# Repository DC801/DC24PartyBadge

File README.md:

# DC801_DC24PartyBadge
Party badge and BLE hardware board

# Hardware
Board design is in Eagle

Board consists of:

Rigado BMD-200 Bluetooth low energy based on a Nordic nRF51822
 - 16MHz ARM® Cortex™ M0 CPU, 256kB of flash memory, 32kB RAM
 - https://www.rigado.com/product/bmd-200/

 - 2 RGB LEDs
 - 10 orange LEDs addressable in pairs
 - Single button
 - A MCP73831 LiPo battery charger
 - Spare pins (I2C)
 - JTAG interface
 - Micro USB - for charging only
 - Kickass silkscreen

# Software
Environment is the nRFgo Studio and Keil
need a segger j-link programmer
custom_board.h goes in the C:\Keil_v5\ARM\Pack\NordicSemiconductor\nRF_Examples\11.0.0-2.alpha\bsp
Uses the soft device s130v1 firmware

Device is programmed with the softdevice first, then the application is loaded

# What's it do?

The badge, when powered on, will run in one of 5 modes.

- Mode 1 - 'Knight Rider' pattern
- Mode 2 - Alternating red eyes
- Mode 3 - Color strobe eyes
- Mode 4 - Battery indicator - voltage as a percentage of 3.7V.  Each pair lit is 20%, flashing means 10% instead - add the pairs together to get percentage (increases to the right)
- Mode 5 - Randomly firing orange LEDs

In all modes the bluetooth stack is working as an Eddystone, which broadcasts a URL every 100ms.  Newer phones will automatically see the URL and display a notification for it.

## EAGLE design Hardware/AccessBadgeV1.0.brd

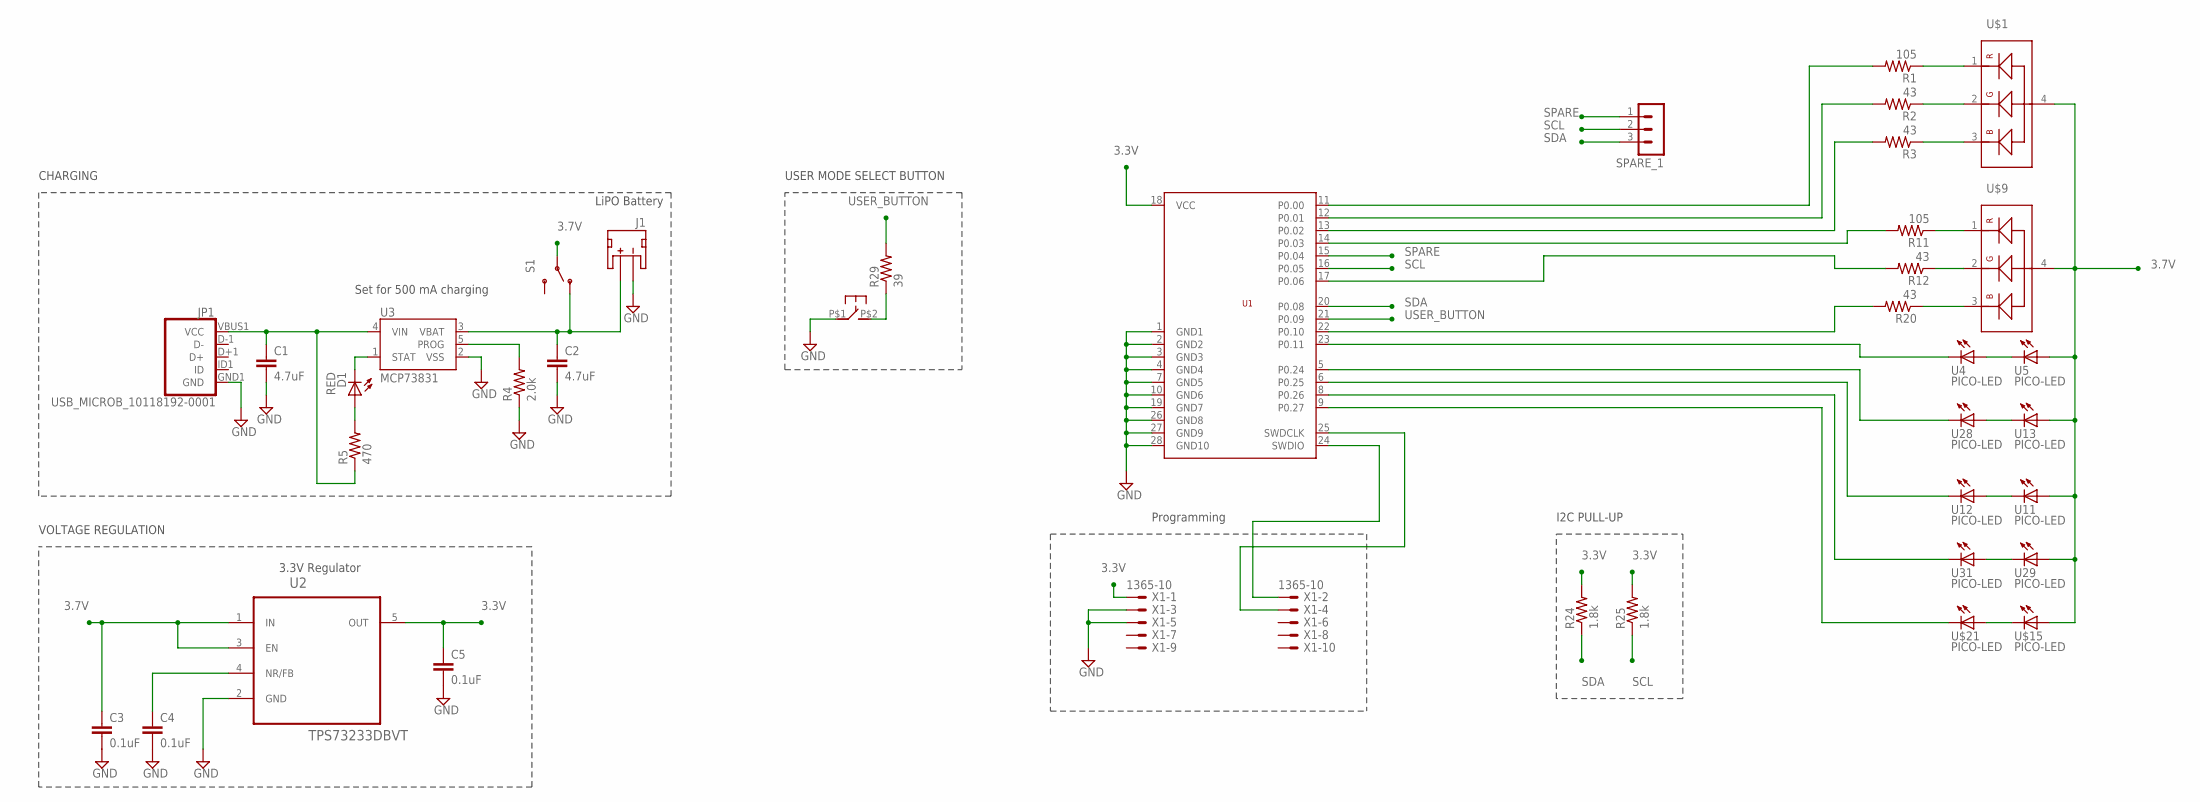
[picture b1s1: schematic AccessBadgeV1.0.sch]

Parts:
C1, C2: 4.7uF; 0603-CAP
C3, C4, C5: 0.1uF; C0201
D1: RED; CHIP-LED0603
J1: JST_2MM_MALE; JST-2-SMD
JP1: USB_MICROB_10118192-0001; USB-B-MICRO-SMD_V03
R1, R11: 105; R0201
R2, R3, R12, R20: 43; R0201
R4: 2.0k; R0201
R5: 470; R0201
R24, R25: 1.8k; R0201
R29: 39; R0201
S1: SWITCH-SPDTSMD2; SWITCH-SPDT-SMD
SLC: TACTILE_BUTTON; KXT131
SPARE_1: MA03-1
U1: BMD-200
U2: TPS73233DBVT; SOT95P280X145-5N
U3: MCP73831; SOT23-5
U4, U5, U11, U12, U13, U28, U29, U31: PICO-LED; CHIP-LED0402
U$1, U$9: RGB; 0606
U$15, U$21: PICO-LED; CHIP-LED0402
X1: 1365-10

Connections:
3.3V: C5.1, R24.2, R25.2, U1.18 (VCC), U2.5 (OUT), X1.1
3.7V: C3.1, S1.2, U2.1 (IN), U2.3 (EN), U5.P$1 (A), U11.P$1 (A), U13.P$1 (A), U29.P$1 (A), U$1.4, U$9.4, U$15.P$1 (A)
GND: C1.2, C2.2, C3.2, C4.2, C5.2, J1.1 (-), JP1.GND1 (GND), R4.1, SLC.P$1, U1.1 (GND1), U1.2 (GND2), U1.3 (GND3), U1.4 (GND4), U1.7 (GND5), U1.10 (GND6), U1.19 (GND7), U1.26 (GND8), U1.27 (GND9), U1.28 (GND10), U2.2 (GND), U3.2 (VSS), X1.3, X1.5
unnamed: R1.2, U1.11 (P0.00)
unnamed: R2.2, U1.12 (P0.01)
unnamed: R3.2, U1.13 (P0.02)
unnamed: R11.2, U1.14 (P0.03)
unnamed: U1.5 (P0.24), U28.P$2 (C)
unnamed: U1.9 (P0.27), U$21.P$2 (C)
unnamed: U4.P$1 (A), U5.P$2 (C)
unnamed: U1.23 (P0.11), U4.P$2 (C)
unnamed: R1.1, U$1.1
unnamed: R2.1, U$1.2
unnamed: R3.1, U$1.3
unnamed: R4.2, U3.5 (PROG)
unnamed: C1.1, JP1.VBUS1 (VCC), R5.1, U3.4 (VIN)
unnamed: D1.A, R5.2
unnamed: D1.C, U3.1 (STAT)
unnamed: R11.1, U$9.1
unnamed: R12.1, U$9.2
unnamed: C4.1, U2.4 (NR/FB)
unnamed: U$15.P$2 (C), U$21.P$1 (A)
unnamed: U29.P$2 (C), U31.P$1 (A)
unnamed: U11.P$2 (C), U12.P$1 (A)
unnamed: U13.P$2 (C), U28.P$1 (A)
unnamed: R20.1, U$9.3
unnamed: U1.8 (P0.26), U31.P$2 (C)
unnamed: U1.6 (P0.25), U12.P$2 (C)
unnamed: R20.2, U1.22 (P0.10)
unnamed: R12.2, U1.17 (P0.06)
unnamed: R29.1, SLC.P$2
unnamed: U1.24 (SWDIO), X1.2
unnamed: U1.25 (SWDCLK), X1.4
SCL: R25.1, SPARE_1.2, U1.16 (P0.05)
SDA: R24.1, SPARE_1.3, U1.20 (P0.08)
SPARE: SPARE_1.1, U1.15 (P0.04)
USER_BUTTON: R29.2, U1.21 (P0.09)
VBAT1: C2.1, J1.2 (+), S1.1 (O), U3.3 (VBAT)

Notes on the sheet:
Programming
I2C PULL-UP
LiPO Battery
Set for 500 mA charging
3.3V Regulator
USER MODE SELECT BUTTON
CHARGING
VOLTAGE REGULATION

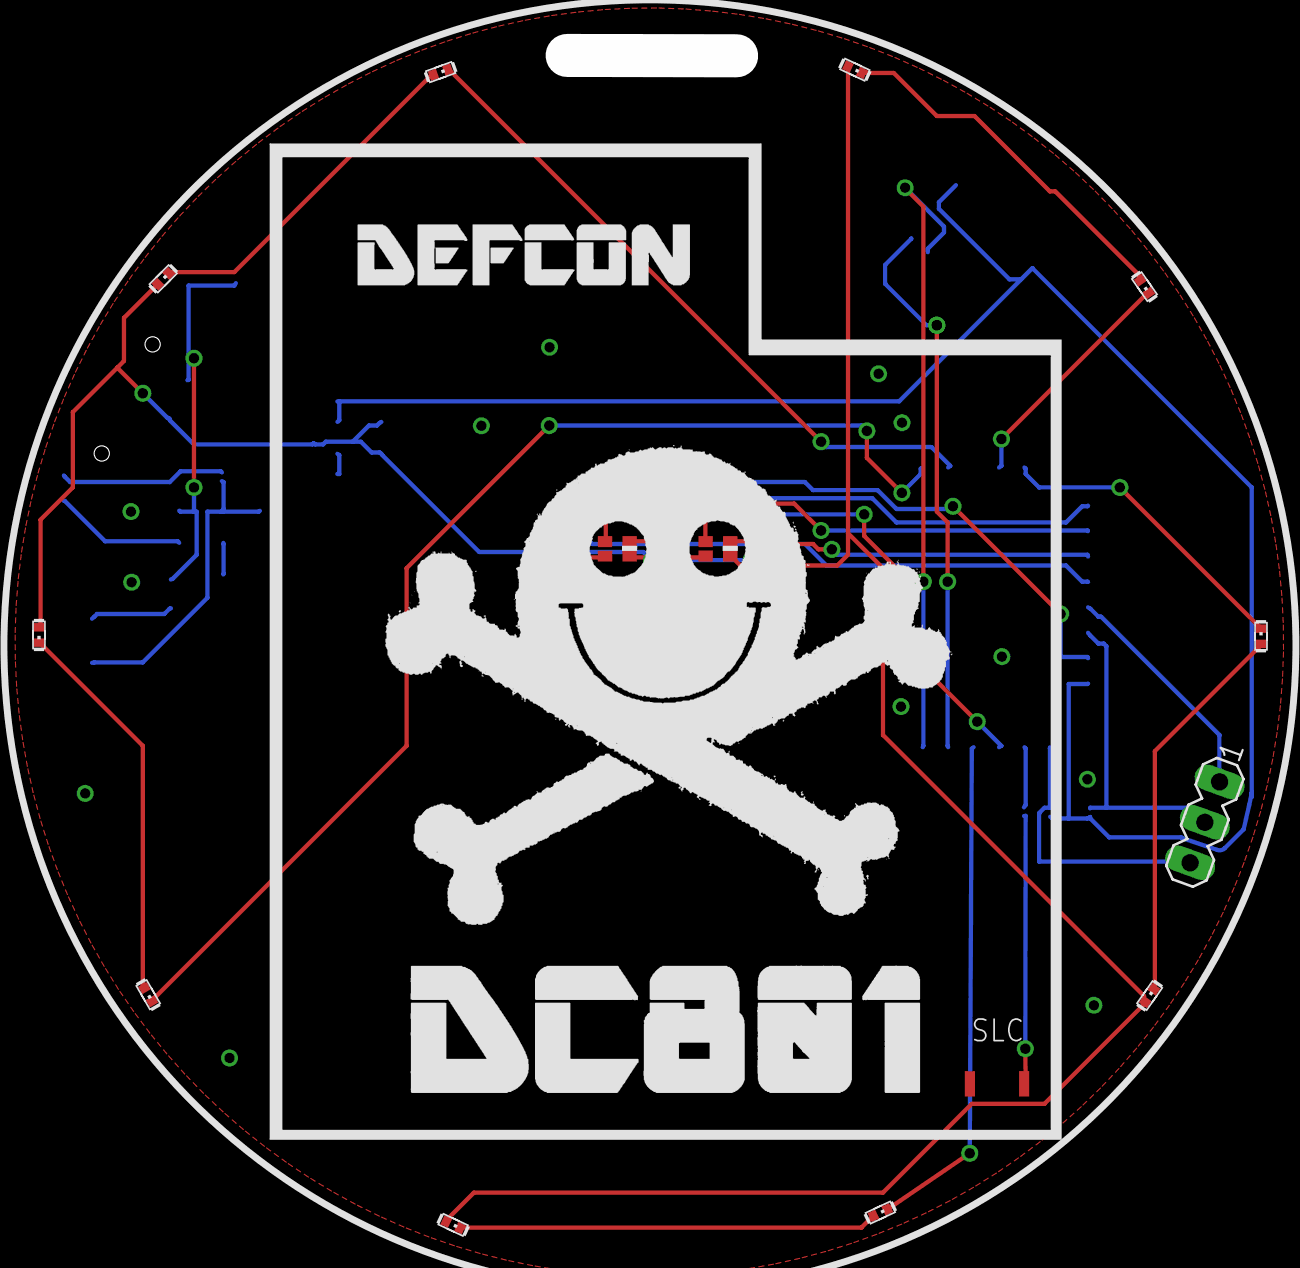
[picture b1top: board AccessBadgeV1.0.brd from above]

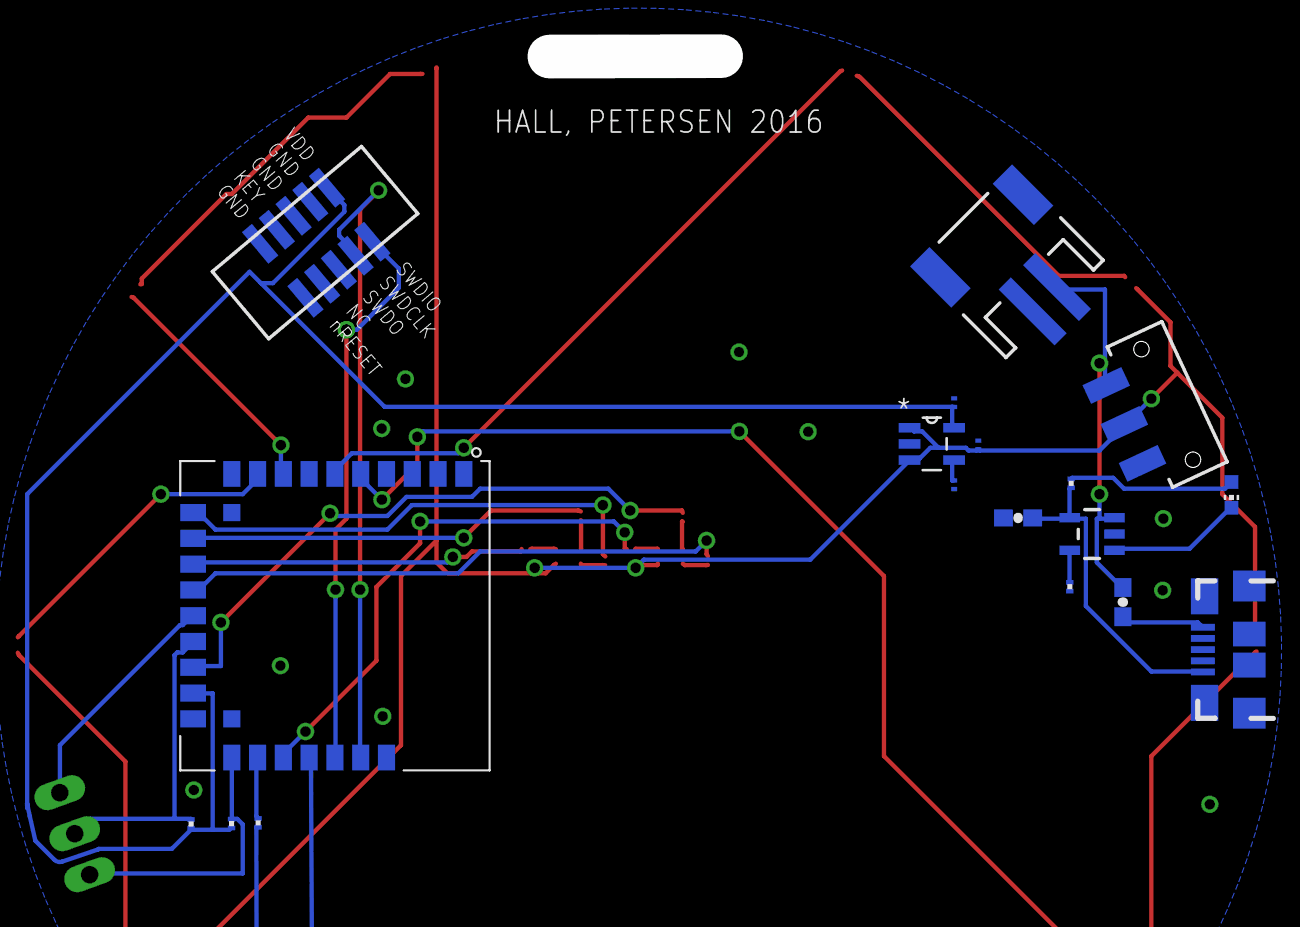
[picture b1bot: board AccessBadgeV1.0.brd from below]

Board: 2 copper layers, 38 parts (18 on the bottom side), 38 nets.

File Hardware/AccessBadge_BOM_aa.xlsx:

Mfg Part # | Ref. Des. | Description Value Pkg |  |  |  | QTY | DNI | NOTES
CL10A475KQ5LNNC | C1, C2 | CAPACITOR, 4.7uF, C0603 |  |  |  | 2
GRM033R60J104KE19D | C3, C4, C5 | CAPACITOR, 0.1uF, C0201 |  |  |  | 3
SML-D12V1WT86 | D1 | RED, LEDCHIP-LED0603 |  |  |  | 1
S2B-PH-SM4-TB(LF)(SN) | J1 | JST_2MM_MALE, JST-2-SMD, Mates to single-cell LiPo batteries |  |  |  | 1
10118192-0001LF | JP1 | USB_MICROB_PLUGCONN-11752, USB-B-MICRO-SMD_V03, USB Micro-B Plug |  |  |  | 1
3220-10-0300-00 | x1 | 10 Positions Header, Shrouded Connector 0.050" (1.27mm) Surface Mount Gold |  |  |  | 1 |  | Digikey # 1175-1629-ND
KXT 131 LHS | SLC | TACTILE_BUTTON, KXT131 |  |  |  | 1
RMCF0201JT2K00 | R4 | RESISTOR, 2.0k, R0201 |  |  |  | 1
RMCF0201JT470R | R5 | RESISTOR, 470, R0201 |  |  |  | 1
RC0201FR-07105RL | R1, R11 | RESISTOR, 105, R0201 |  |  |  | 2
RC0201JR-0743RL | R2, R3, R12, R20 | RESISTOR, 43, R0201 |  |  |  | 4
RMCF0201JT1K80 | R24, R25 | RESISTOR, 1.8k, R0201 |  |  |  | 2
RC0201JR-0739RL | R29 | RESISTOR, 39, R0201 |  |  |  | 1
JS102011SAQN | S1 | SWITCH-SPDTSMD2, SWITCH-SPDT-SMD, SPDT Switch |  |  |  | 1
 | SPARE_1 | MA03-1, PIN HEADER |  |  |  | 0 | DNI
LTST-C19HE1WT | U$1, U$9 | RGB, 606 |  |  |  | 2 |  | Lite-On
TPS73233DBVT | U2 | Cap-Free, NMOS, 250mA Low Dropout Regulator with Reverse Current Protection, SO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 |  |  |  | 1 |  | Texas Instruments
MCP73831T-2ACI/OT | U3 | MCP73831, SOT23-5, Microchip's MCP73831 |  |  |  | 1
SML-P11DTT86 | U4, U5, U11, U12, U13, U28, U29, U31, U$15, U$21 | PICO-LED, CHIP-LED0402 |  |  |  | 10 |  | ROHM orange LED
BMD-200-B-R | U1 | BMD-200 |  |  |  | 1 |  | Buying straight from might be cheapest Rigado LLC Want the rev B version

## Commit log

2016-07-15 Base Code for board
    Base code for board
2016-07-15 Update main.c
    updated main.c with better code
    purple eyes fast orange ring
2016-07-16 Clean up of directory structure, fleshing out the readme a little more
2016-07-16 Fixed readme layout
2016-07-16 new commit
2016-08-03 Adding code to monitor and react to the button being pressed Adding a few LED display modes Adding some different eddystone URLs
2016-08-03 Updated the description
2016-08-03 Fixed description layout
2016-08-03 Adding seizure mode for long press of the button

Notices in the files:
parts and their libraries:
SparkFun: Licensing: CC v3.0 Share-Alike You are welcome to use this library for commercial purposes.
SparkFun-Connectors: Licensing: Creative Commons ShareAlike 4.0 International - https://creativecommons.org/licenses/by-sa/4.0
